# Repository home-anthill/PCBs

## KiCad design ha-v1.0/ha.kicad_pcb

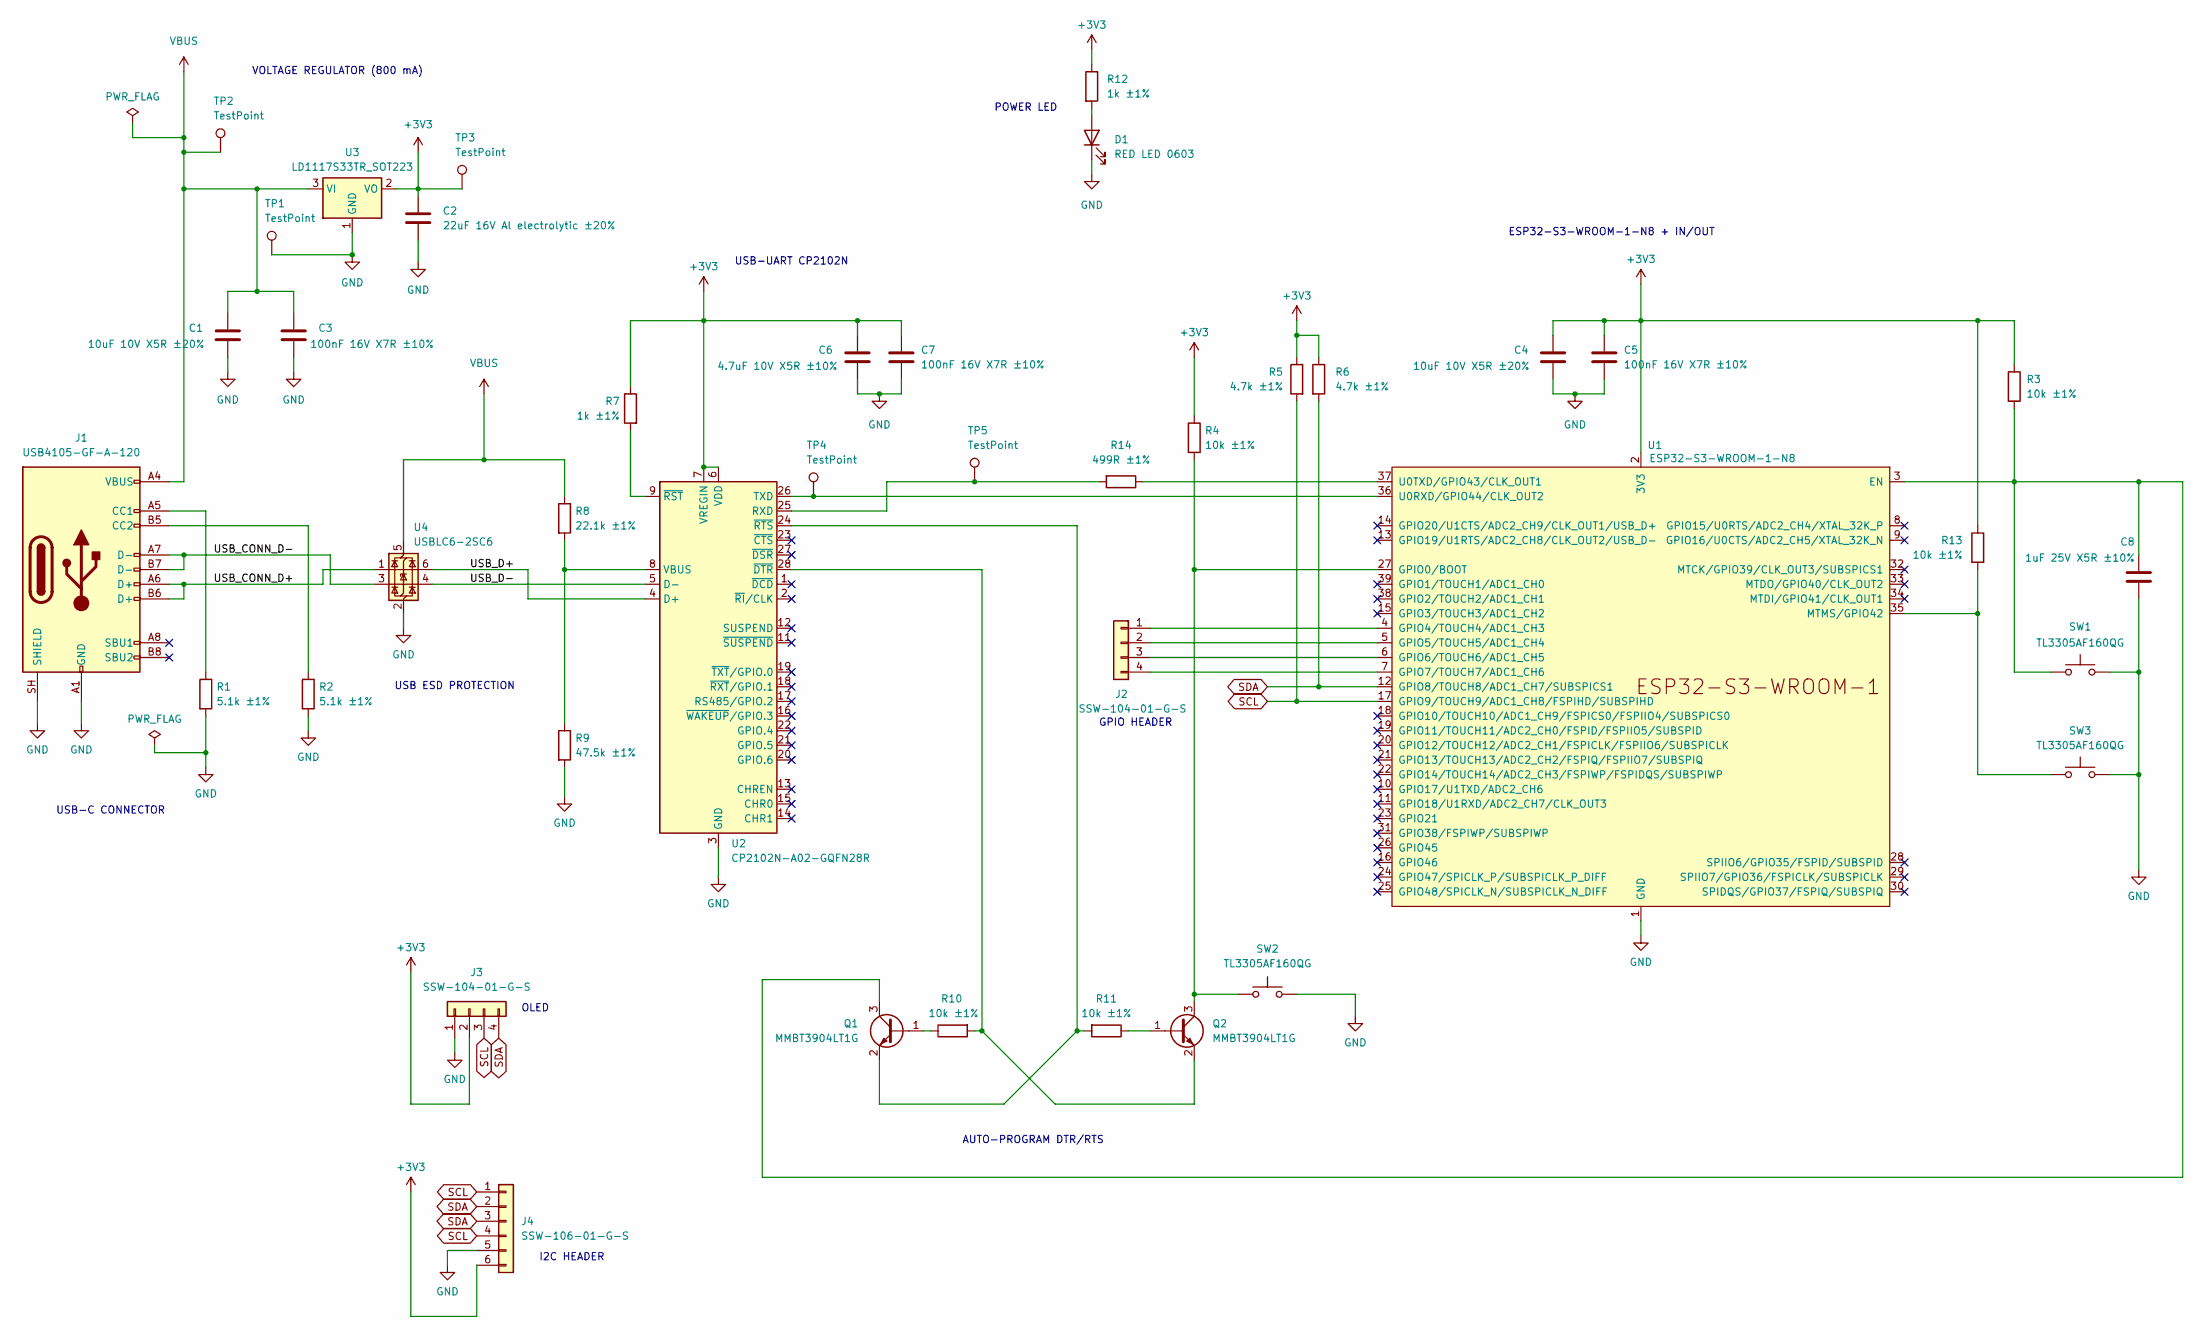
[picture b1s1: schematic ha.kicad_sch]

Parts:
C1, C4: 10uF 10V X5R ±20%; C_0805_2012Metric; MPN CC0805MKX5R6BB106
C2: 22uF 16V Al electrolytic ±20%; CP_Elec_4x5.8; MPN EEE-FK1C220UR
C3, C5, C7: 100nF 16V X7R ±10%; C_0603_1608Metric; MPN CC0603KRX7R7BB104
C6: 4.7uF 10V X5R ±10%; C_0805_2012Metric; MPN CC0805KKX5R6BB475
C8: 1uF 25V X5R ±10%; C_0603_1608Metric; MPN CC0603KRX5R8BB105
D1: RED LED 0603; LED_0603_1608Metric; MPN APTD1608LSURCK
J1: USB4105-GF-A-120; USB_C_Receptacle_GCT_USB4105-xx-A_16P_TopMnt_Horizontal; MPN USB4105-GF-A-120
J2, J3: SSW-104-01-G-S; PinSocket_1x04_P2.54mm_Vertical; MPN SSW-104-01-G-S
J4: SSW-106-01-G-S; PinSocket_1x06_P2.54mm_Vertical; MPN SSW-106-01-G-S
Q1, Q2: MMBT3904LT1G; SOT-23; MPN MMBT3904LT1G
R1, R2: 5.1k ±1%; R_0603_1608Metric; MPN RC0603FR-075K1L
R3, R4, R10, R11, R13: 10k ±1%; R_0603_1608Metric; MPN RC0603FR-0710KL
R5, R6: 4.7k ±1%; R_0603_1608Metric; MPN RC0603FR-074K7L
R7, R12: 1k ±1%; R_0603_1608Metric; MPN RC0603FR-071KL
R8: 22.1k ±1%; R_0603_1608Metric; MPN RC0603FR-0722K1L
R9: 47.5k ±1%; R_0603_1608Metric; MPN RC0603FR-0747K5L
R14: 499R ±1%; R_0603_1608Metric; MPN RC0603FR-07499RL
SW1, SW2, SW3: TL3305AF160QG; SW_SPST_TL3305A; MPN TL3305AF160QG
TP1, TP2, TP3: TestPoint; TestPoint_Pad_D1.5mm
TP4, TP5: TestPoint; TestPoint_Pad_D1.0mm
U1: ESP32-S3-WROOM-1-N8; ESP32-S3-WROOM-1; MPN ESP32-S3-WROOM-1-N8
U2: CP2102N-A02-GQFN28R; QFN-28-1EP_5x5mm_P0.5mm_EP3.35x3.35mm; MPN CP2102N-A02-GQFN28R
U3: LD1117S33TR_SOT223; SOT-223-3_TabPin2; MPN LD1117S33TR
U4: USBLC6-2SC6; SOT-23-6; MPN USBLC6-2SC6

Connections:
+3V3: C2.1, C4.1, C5.1, C6.1, C7.1, J3.2, J4.6, R3.1, R4.1, R5.1, R6.1, R7.1, R12.1, R13.1, TP3.1 (1_1), U1.2 (3V3), U2.6 (VDD), U2.7 (VREGIN), U3.2 (VO)
/USB_CONN_D+: J1.A6 (D+), J1.B6 (D+), U4.1 (I/O1)
/USB_CONN_D-: J1.A7 (D-), J1.B7 (D-), U4.3 (I/O2)
/USB_D+: U2.4 (D+), U4.6 (I/O1)
/USB_D-: U2.5 (D-), U4.4 (I/O2)
GND: C1.2, C2.2, C3.2, C4.2, C5.2, C6.2, C7.2, C8.2, D1.1 (K), J1.A1 (GND), J1.A12 (GND), J1.B1 (GND), J1.B12 (GND), J1.SH (SHIELD), J3.1, J4.5, R1.2, R2.2, R9.2, SW1.2, SW2.2, SW3.2, TP1.1 (1_1), U1.1 (GND), U1.40 (GND), U1.41 (GND), U2.3 (GND), U2.29 (GND), U3.1 (GND), U4.2 (GND)
unnamed: D1.2 (A), R12.2
unnamed: J1.A5 (CC1), R1.1
unnamed: J1.B5 (CC2), R2.1
unnamed: J2.1, U1.4 (GPIO4/TOUCH4/ADC1_CH3)
unnamed: J2.2, U1.5 (GPIO5/TOUCH5/ADC1_CH4)
unnamed: J2.3, U1.6 (GPIO6/TOUCH6/ADC1_CH5)
unnamed: J2.4, U1.7 (GPIO7/TOUCH7/ADC1_CH6)
unnamed: Q1.1 (B), R10.1
unnamed: C8.1, Q1.3 (C), R3.2, SW1.1, U1.3 (EN)
unnamed: Q1.2 (E), R11.2, U2.24 (~RTS)
unnamed: Q2.1 (B), R11.1
unnamed: Q2.3 (C), R4.2, SW2.1, U1.27 (GPIO0/BOOT)
unnamed: Q2.2 (E), R10.2, U2.28 (~DTR)
unnamed: R13.2, SW3.1, U1.35 (MTMS/GPIO42)
unnamed: TP4.1 (1_1), U1.36 (U0RXD/GPIO44/CLK_OUT2), U2.26 (TXD)
unnamed: R14.1, U1.37 (U0TXD/GPIO43/CLK_OUT1)
unnamed: R14.2, TP5.1 (1_1), U2.25 (RXD)
unnamed: R8.2, R9.1, U2.8 (VBUS)
unnamed: R7.2, U2.9 (~RST)
SCL: J3.3, J4.1, J4.4, R5.2, U1.17 (GPIO9/TOUCH9/ADC1_CH8/FSPIHD/SUBSPIHD)
SDA: J3.4, J4.2, J4.3, R6.2, U1.12 (GPIO8/TOUCH8/ADC1_CH7/SUBSPICS1)
VBUS: C1.1, C3.1, J1.A4 (VBUS), J1.A9 (VBUS), J1.B4 (VBUS), J1.B9 (VBUS), R8.1, TP2.1 (1_1), U3.3 (VI), U4.5 (VBUS)

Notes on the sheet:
USB-C CONNECTOR
AUTO-PROGRAM DTR/RTS
OLED
POWER LED
I2C HEADER
ESP32-S3-WROOM-1-N8 + IN/OUT
USB-UART CP2102N
GPIO HEADER
VOLTAGE REGULATOR (800 mA)
USB ESD PROTECTION

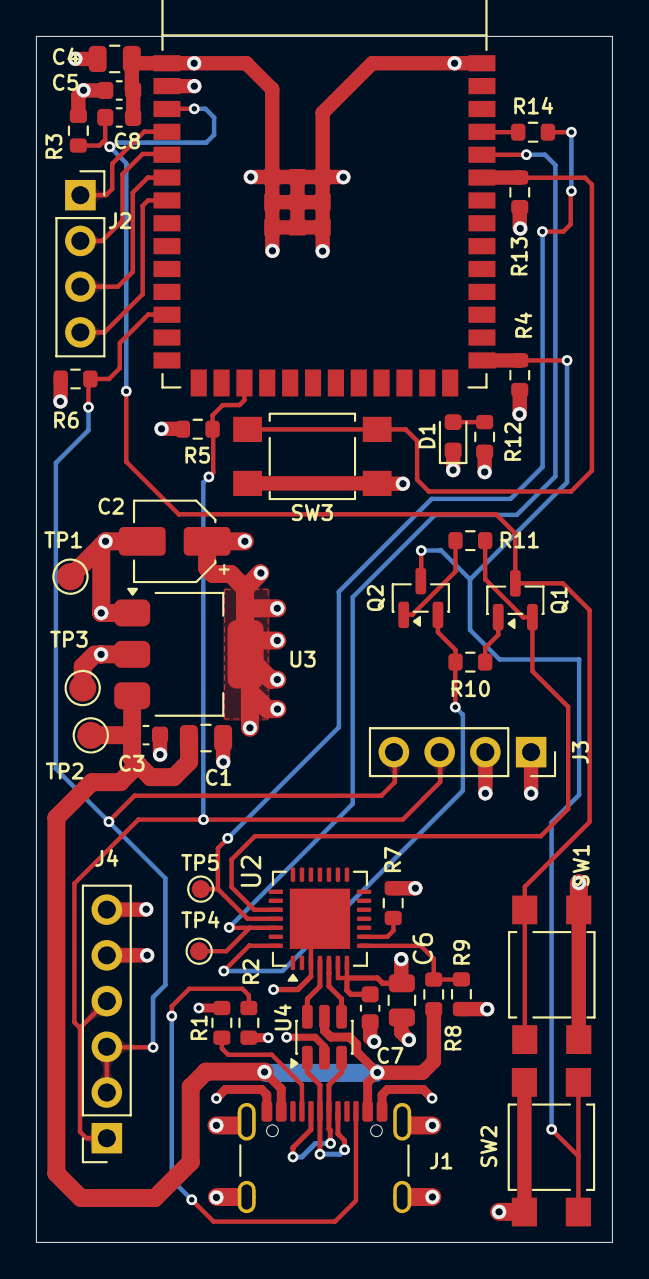
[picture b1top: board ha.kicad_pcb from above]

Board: 4 copper layers, 32.0 x 67.0 mm, 41 parts (0 on the bottom side), 28 nets.

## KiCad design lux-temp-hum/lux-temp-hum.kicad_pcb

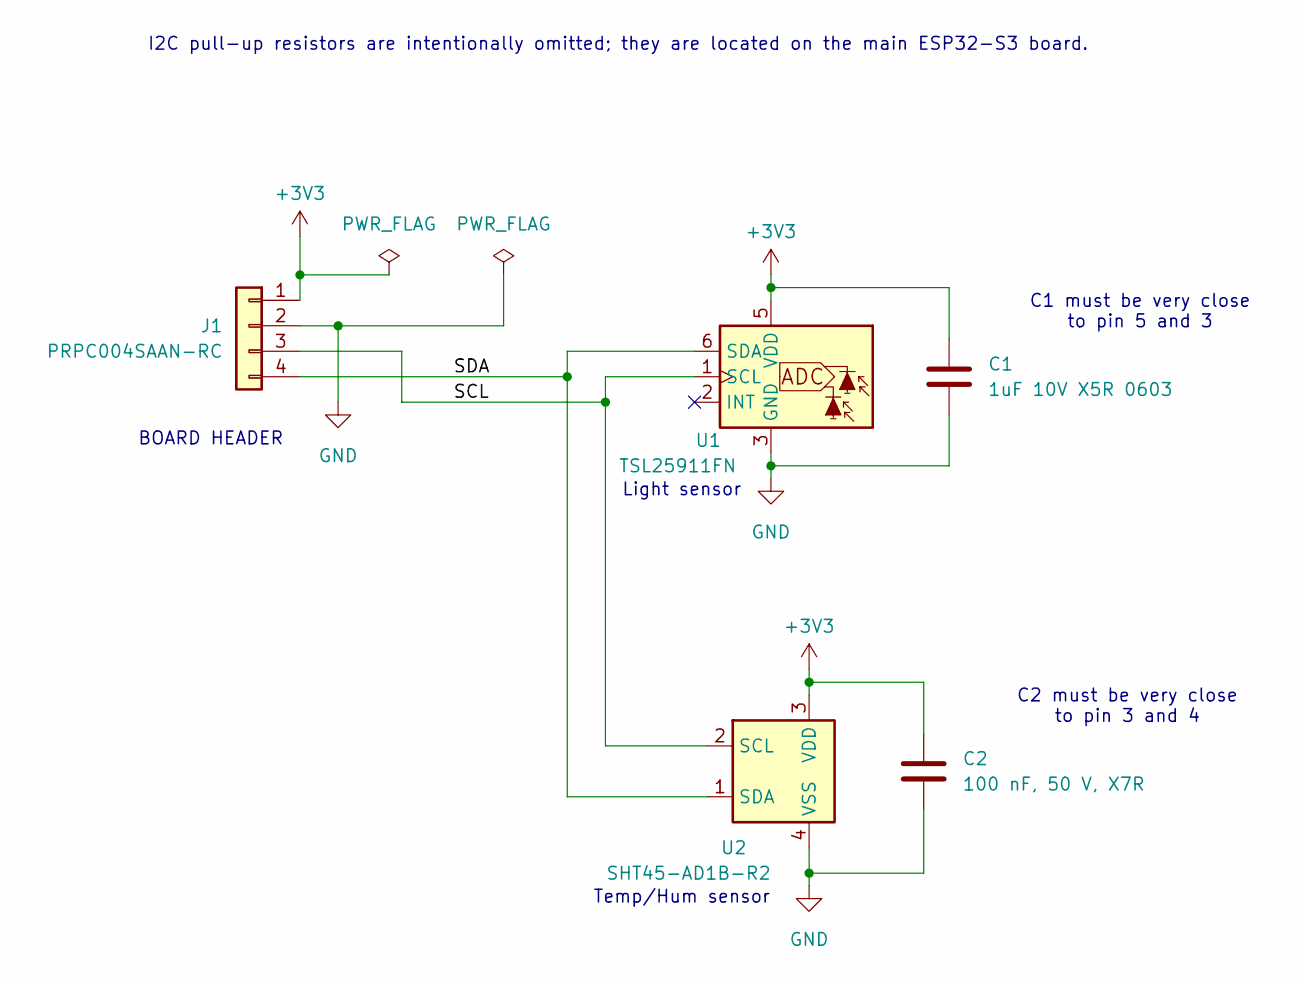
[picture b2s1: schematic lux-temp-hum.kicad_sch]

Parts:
C1: 1uF 10V X5R 0603; C_0603_1608Metric; MPN GRM188R61A105KA61D; Digi-Key Part Number 490-1543-1-ND
C2: 100 nF, 50 V, X7R; C_0603_1608Metric; MPN C0603C104K5RACTU; Digi-Key Part Number 399-C0603C104K5RACTUCT-ND
J1: PRPC004SAAN-RC; PinHeader_1x04_P2.54mm_Vertical; MPN PRPC004SAAN-RC; Digi-Key Part Number 35-PRPC004SAAN-RC-ND
U1: TSL25911FN; AMS_TSL25911FN; MPN TSL25911FN; Digi-Key Part Number TSL25911FNCT-ND
U2: SHT45-AD1B-R2; Sensirion_DFN-4_1.5x1.5mm_P0.8mm_SHT4x_NoCentralPad; MPN SHT45-AD1B-R2; Digi-Key Part Number 1649-SHT45-AD1B-R2CT-ND

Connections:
+3V3: C1.1, C2.1, J1.1, U1.5 (VDD), U2.3 (VDD)
/SCL: J1.3, U1.1 (SCL), U2.2 (SCL)
/SDA: J1.4, U1.6 (SDA), U2.1 (SDA)
GND: C1.2, C2.2, J1.2, U1.3 (GND), U2.4 (VSS)

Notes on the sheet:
I2C pull-up resistors are intentionally omitted; they are located on the main ESP32-S3 board.
C2 must be very close to pin 3 and 4
Light sensor
BOARD HEADER
Temp/Hum sensor
C1 must be very close to pin 5 and 3

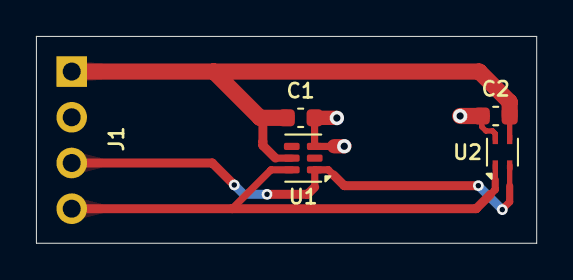
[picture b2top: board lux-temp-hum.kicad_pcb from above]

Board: 2 copper layers, 27.8 x 11.5 mm, 5 parts (1 on the bottom side), 4 nets.
